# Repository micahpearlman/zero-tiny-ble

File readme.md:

## Overview

The Zero Tiny BLE is a small low cost and low powered embeddable board with an AVR ATTiny85 microcontroller and a Bluetooth 4.0 (Bluetooth Low Energy or BLE) radio.

* AVR ATTiny85 microcontroller running at 8MHz internal clock and 3.3V. [ATTiny85 Datasheet](http://www.atmel.com/images/atmel-2586-avr-8-bit-microcontroller-attiny25-attiny45-attiny85_datasheet.pdf).
* HM-10 Bluetooth 4.0 Low Energy module.  [HM-10 Datasheet](http://www.jnhuamao.cn/bluetooth40_en.zip).
* Powered by single cell 3.7V Lithium Polymer battery (LiPo) or USB B mini port.
* LiPo battery recharge capabilities via the USB B mini port.
* Standard UART communication over Bluetooth 4.0.
* Easy prototyping via breadboard.
* Use either Arduino or AVR-GCC development environments.
* Small form factor of 20mm x 47mm (0.79” x 1.85”)
* You can purchase a complete board at [Tindie](https://www.tindie.com/products/micahpearlman/zero-tiny-ble/)
* You can order unpopulated boards from [OSH Park](https://oshpark.com/shared_projects/1aQHSlM2)

## Why?

This is a project that fell out of developing sensors (Exhaust Gas Temp, RPM, Lap Timer, etc) for my vintage road racing motorcycle.  I also wanted to use my iOS device as the display and data logger.  So I needed a small, cheap and general purpose board that had  uC and BLE capabilities and could be powered by a small LiPo battery (and be charged by a USB connection).  The HM-10 BLE was super cheap and incredibly easy to integrate. The ATTiny85 is also super cheap, requires practically zero external components when running on it's internal oscillator and can be programmed in the Arduino IDE. 

## Pinouts

## Programming Notes
* See our [Getting Started Guide](https://github.com/micahpearlman/zero-tiny-ble/blob/master/docs/zero-tiny-ble-getting-started-guide.md)
* The ATTiny85 cannot be programmed in circuit.  It must be removed and a separate programmer such as the excellent [Sparkfun Tiny AVR Programmer](https://www.sparkfun.com/products/11801).  
* The ATTiny85 pins PB3 (RX) and PB4 (TX) are used for serial communication with the Bluetooth 4.0 radio.
* The ATTiny85 does not have hardware UART serial.  The Arduino SoftwareSerial library should be used. Example:

```
#  define rxPin 3
#  define txPin 4
SoftwareSerial _bluetoothSerial = SoftwareSerial(rxPin, txPin);

void setup() {
	// initialize serial communications at 9600 bps:
	_bluetoothSerial.begin(9600);
}

void loop() {
	_bluetoothSerial.print(“Hello World”);
}
```

* Important: make sure that when programming your ATiny85 in the Arduino IDE that the board is set to “ATTiny85 (internal 8MHz)”

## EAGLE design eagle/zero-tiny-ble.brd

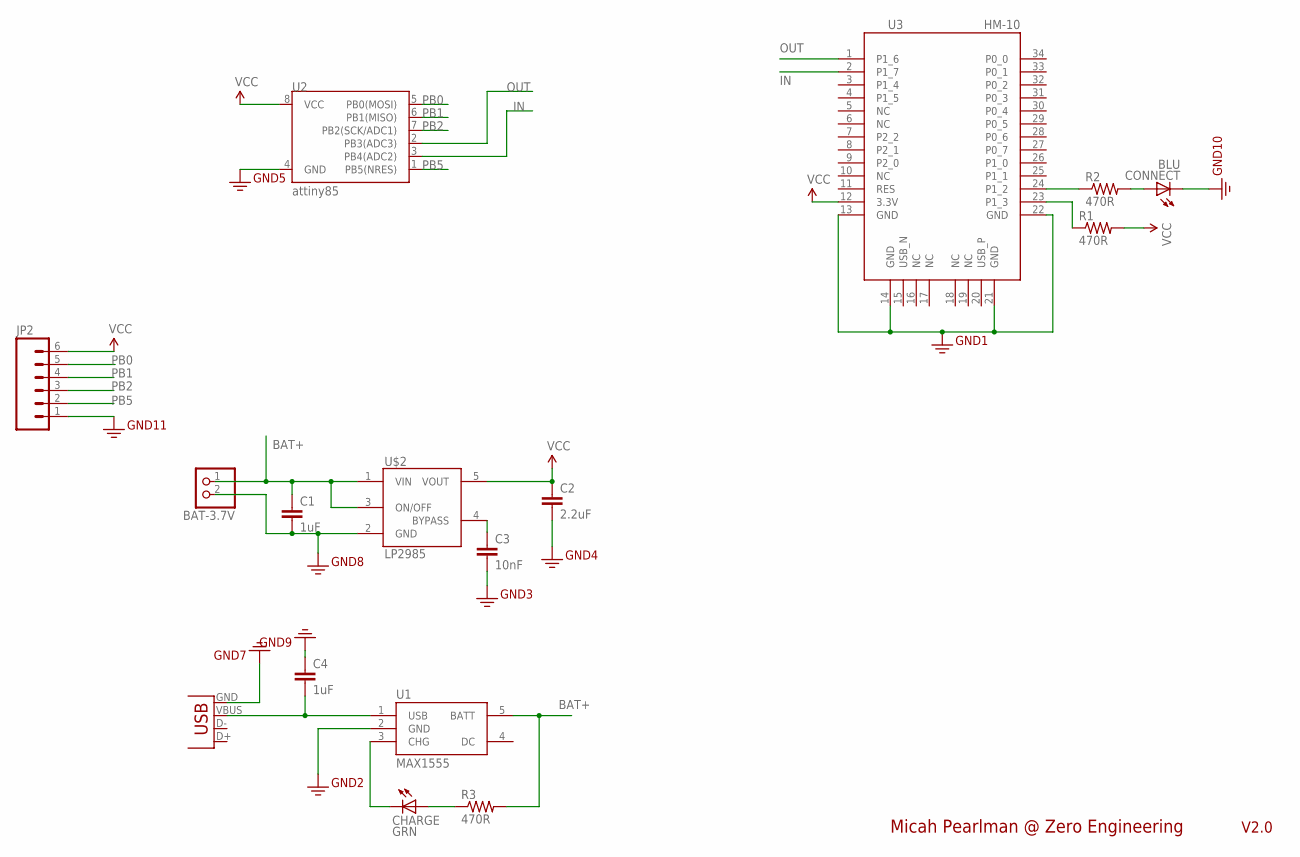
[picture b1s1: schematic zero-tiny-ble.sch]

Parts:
BAT-3.7V: JST_2PIN-THM; JST-PH-2-THM
C1, C4: 1uF; 0805
C2: 2.2uF; 0805
C3: 10nF; 0805
CHARGE: GRN; CHIPLED_0805
CONNECT: BLU; CHIPLED_0805
JP1: USB-SMD-NS; USB-MINIB-NOSTOP
JP2: M06SILK_FEMALE_PTH; 1X06
R1, R2, R3: 470R; 0805
U1: MAX1555; SOT23-5
U2: attiny85; DIP08
U3: HM-10
U$2: LP2985AIM5-3.3; SOT25

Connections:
3.3V: BAT-3.7V.2 (1), C1.2, C2.2, C3.2, C4.1, CONNECT.C, JP1.GND, JP2.1, U1.2 (GND), U2.4 (GND), U3.13 (GND), U3.14 (GND), U3.21 (GND), U3.22 (GND), U$2.2 (GND)
BAT+: BAT-3.7V.1 (2), C1.1, R3.2, U1.5 (BATT), U$2.1 (VIN), U$2.3 (ON/OFF)
BYPASS: C3.1, U$2.4 (BYPASS)
IN: U2.3 (PB4(ADC2)), U3.2 (P1_7)
unnamed: CHARGE.A, R3.1
unnamed: C4.2, JP1.VBUS, U1.1 (USB)
unnamed: CHARGE.C, U1.3 (CHG)
unnamed: R2.1, U3.24 (P1_2)
unnamed: R1.1, U3.23 (P1_3)
unnamed: CONNECT.A, R2.2
OUT: U2.2 (PB3(ADC3)), U3.1 (P1_6)
PB0: JP2.5, U2.5 (PB0(MOSI))
PB1: JP2.4, U2.6 (PB1(MISO))
PB2: JP2.3, U2.7 (PB2(SCK/ADC1))
PB5: JP2.2, U2.1 (PB5(NRES))
VCC: C2.1, JP2.6, R1.2, U2.8 (VCC), U3.12 (3.3V), U$2.5 (VOUT)

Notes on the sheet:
Micah Pearlman @ Zero Engineering
V2.0

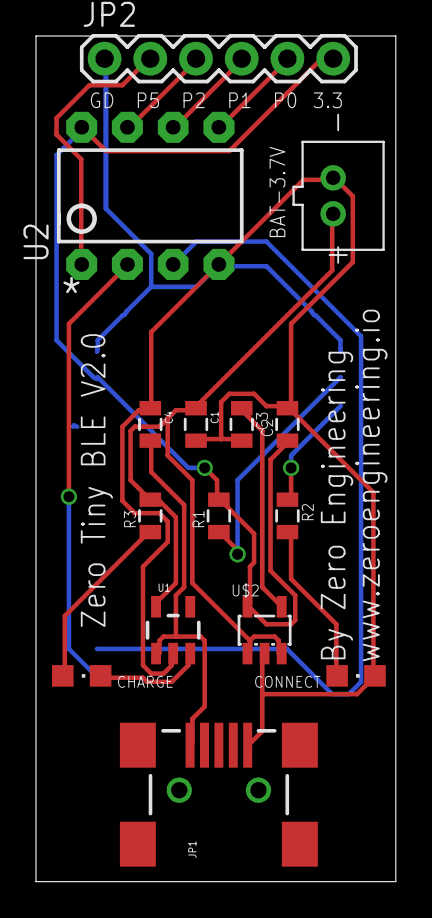
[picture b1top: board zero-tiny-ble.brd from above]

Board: 2 copper layers, 20.0 x 47.0 mm, 16 parts (1 on the bottom side), 16 nets.

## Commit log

2015-01-27 added link to sparkfun tiny programmer
2015-02-02 updated silk screen.
2015-02-02 updated gitignore
2015-02-06 updated pinouts doc
2015-02-07 arduino echo example
2015-02-08 first working iOS example app
2015-02-08 fixed arduino echo example
2015-02-08 added hello world example
2015-02-08 added getting started guide
2015-02-08 updated getting started.

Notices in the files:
parts and their libraries:
SparkFun-Connectors: Licensing: Creative Commons ShareAlike 4.0 International - https://creativecommons.org/licenses/by-sa/4.0
SparkFun-Resistors: Licensing: CC v3.0 Share-Alike You are welcome to use this library for commercial purposes.
